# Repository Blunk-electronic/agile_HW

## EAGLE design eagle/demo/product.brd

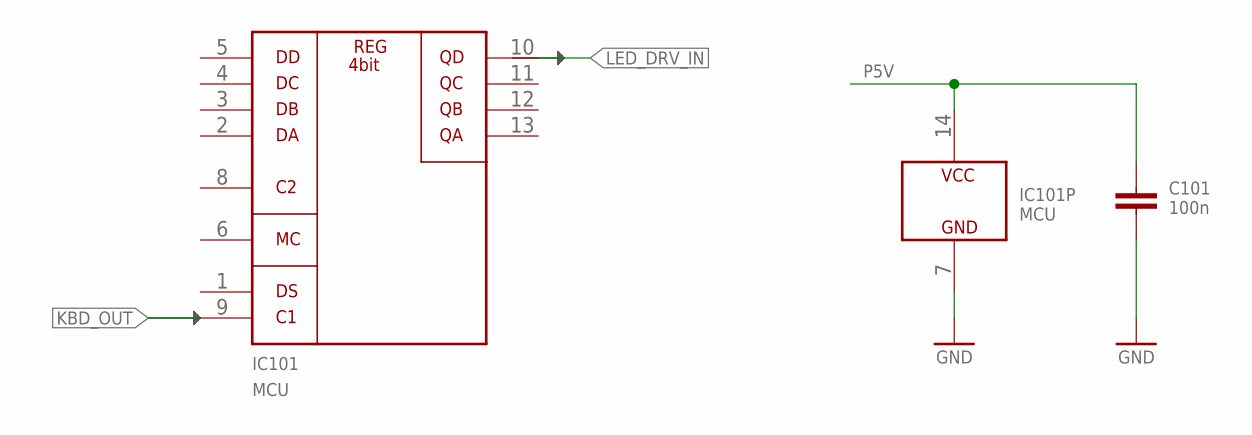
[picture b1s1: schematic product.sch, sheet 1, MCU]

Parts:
C101: 100n; S_0805
IC101: MCU; S_SO14

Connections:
GND: C101.2, IC101.7 (GND); also elsewhere on the board
KBD_OUT: IC101.9 (C1); also elsewhere on the board
LED_DRV_IN: IC101.10 (QD); also elsewhere on the board
P5V: C101.1, IC101.14 (VCC); also elsewhere on the board

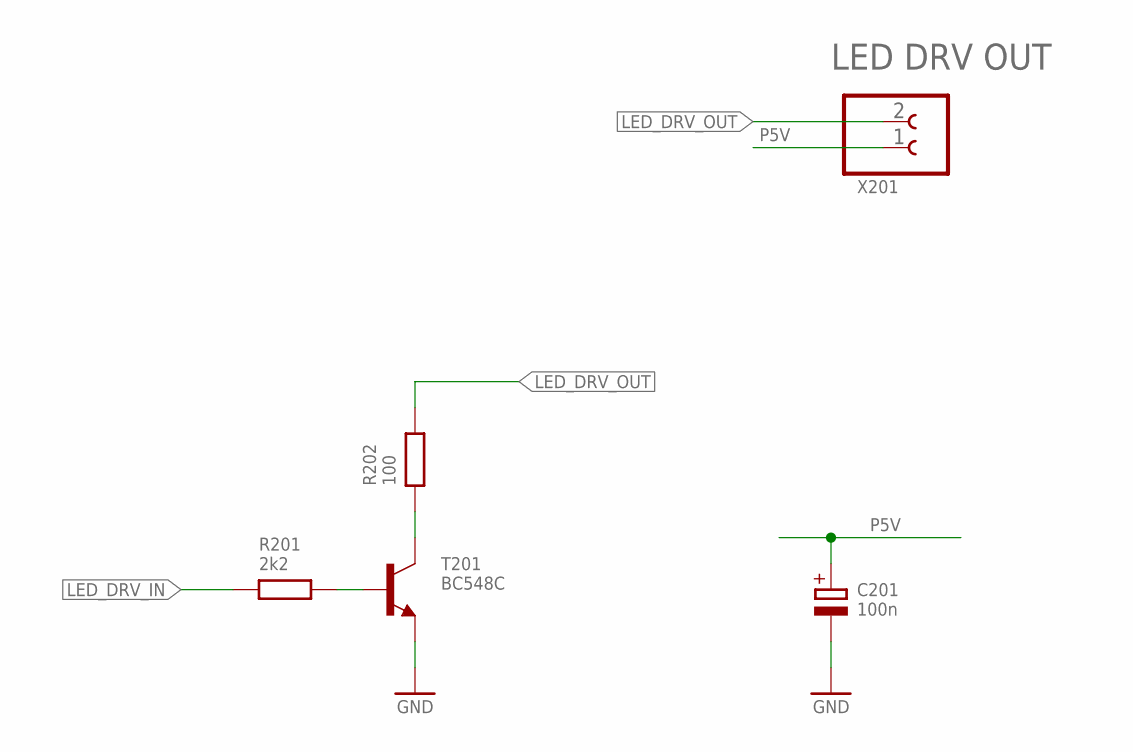
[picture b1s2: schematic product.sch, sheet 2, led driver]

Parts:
C201: 100n; S_6032
R201: 2k2; S_0805
R202: 100; S_0805
T201: BC548C; S_SOT23
X201: CLAMP_1X2-T-2.5MM; T_WIRE_CLAMP_1X2_PITCH_2MM5

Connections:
GND: C201.-, T201.2 (E); also elsewhere on the board
LED_DRV_B: R201.2, T201.1 (B)
LED_DRV_C: R202.1, T201.3 (C)
LED_DRV_IN: R201.1; also elsewhere on the board
LED_DRV_OUT: R202.2, X201.2
P5V: C201.+, X201.1; also elsewhere on the board

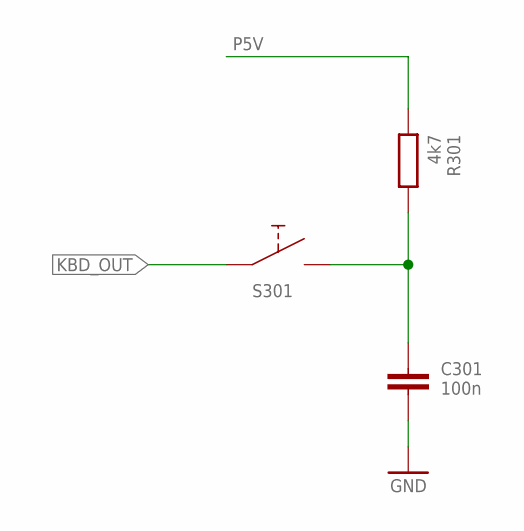
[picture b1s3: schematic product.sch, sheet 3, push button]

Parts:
C301: 100n; S_0805
R301: 4k7; S_0805
S301: PUSH_BUTTON_S_6X6MM; S_PUSH_BUTTON_6X6

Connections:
GND: C301.2; also elsewhere on the board
KBD_OUT: S301.A (A1), S301.A1; also elsewhere on the board
KBD_RC: C301.1, R301.2, S301.B (B1), S301.B1
P5V: R301.1; also elsewhere on the board

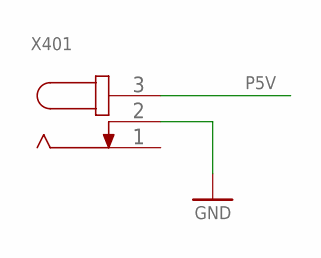
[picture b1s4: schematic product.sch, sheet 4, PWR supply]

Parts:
X401: POWER_JACK-T-0; T_POWER_JACK_SPC4077

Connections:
GND: X401.2; also elsewhere on the board
P5V: X401.3; also elsewhere on the board

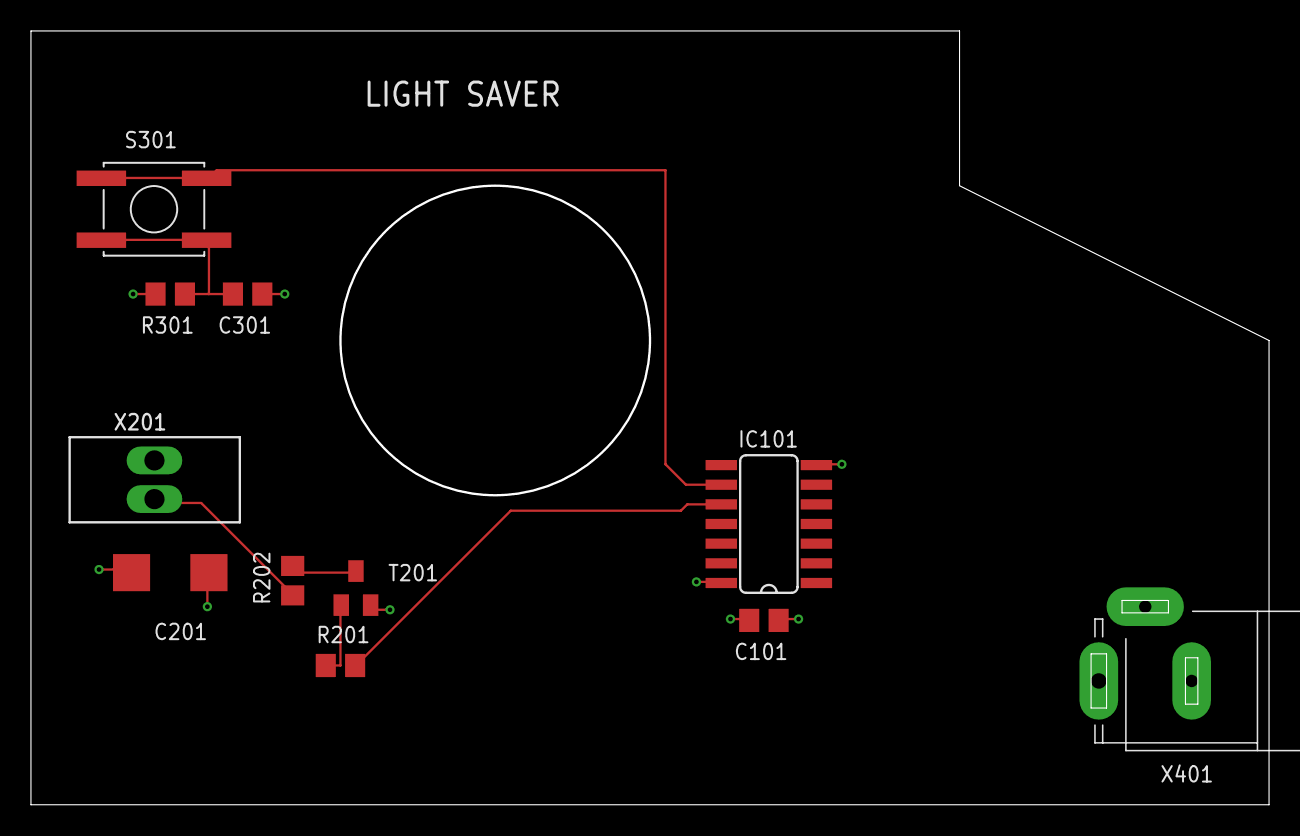
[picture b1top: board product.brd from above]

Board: 4 copper layers, 80.0 x 50.0 mm, 11 parts (0 on the bottom side), 8 nets.

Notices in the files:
parts and their libraries:
be_frame: Copyright(C) Blunk electronic
